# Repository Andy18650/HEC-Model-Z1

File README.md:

# HEC Model Z1
 A Z80 computer with protected mode support
This repository is currently for my own use and for the public to track the progress of the project. 
It is not meant to be used to produce a working computer befor first beta revision is announced.
Any part of this repository may change without notice.

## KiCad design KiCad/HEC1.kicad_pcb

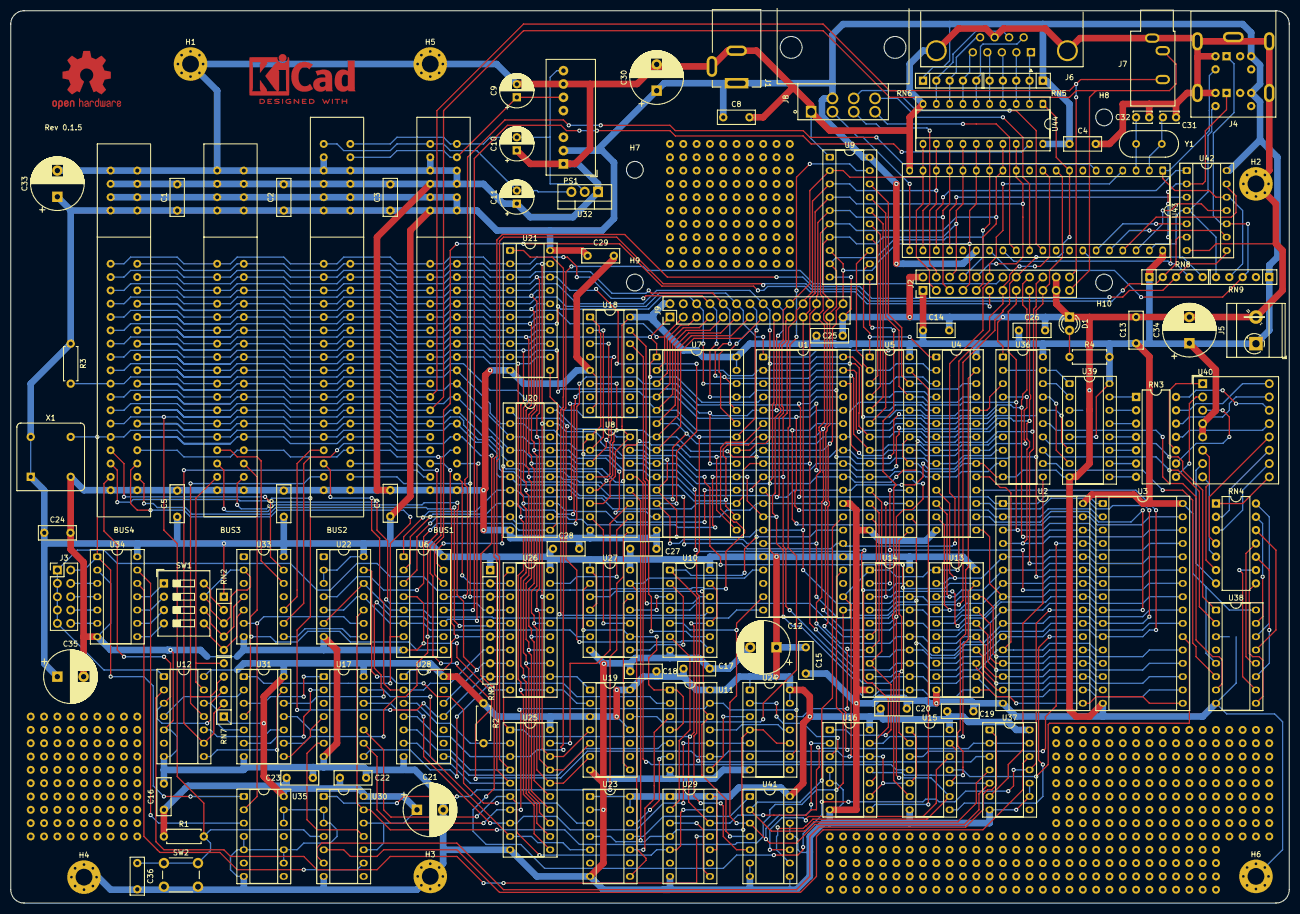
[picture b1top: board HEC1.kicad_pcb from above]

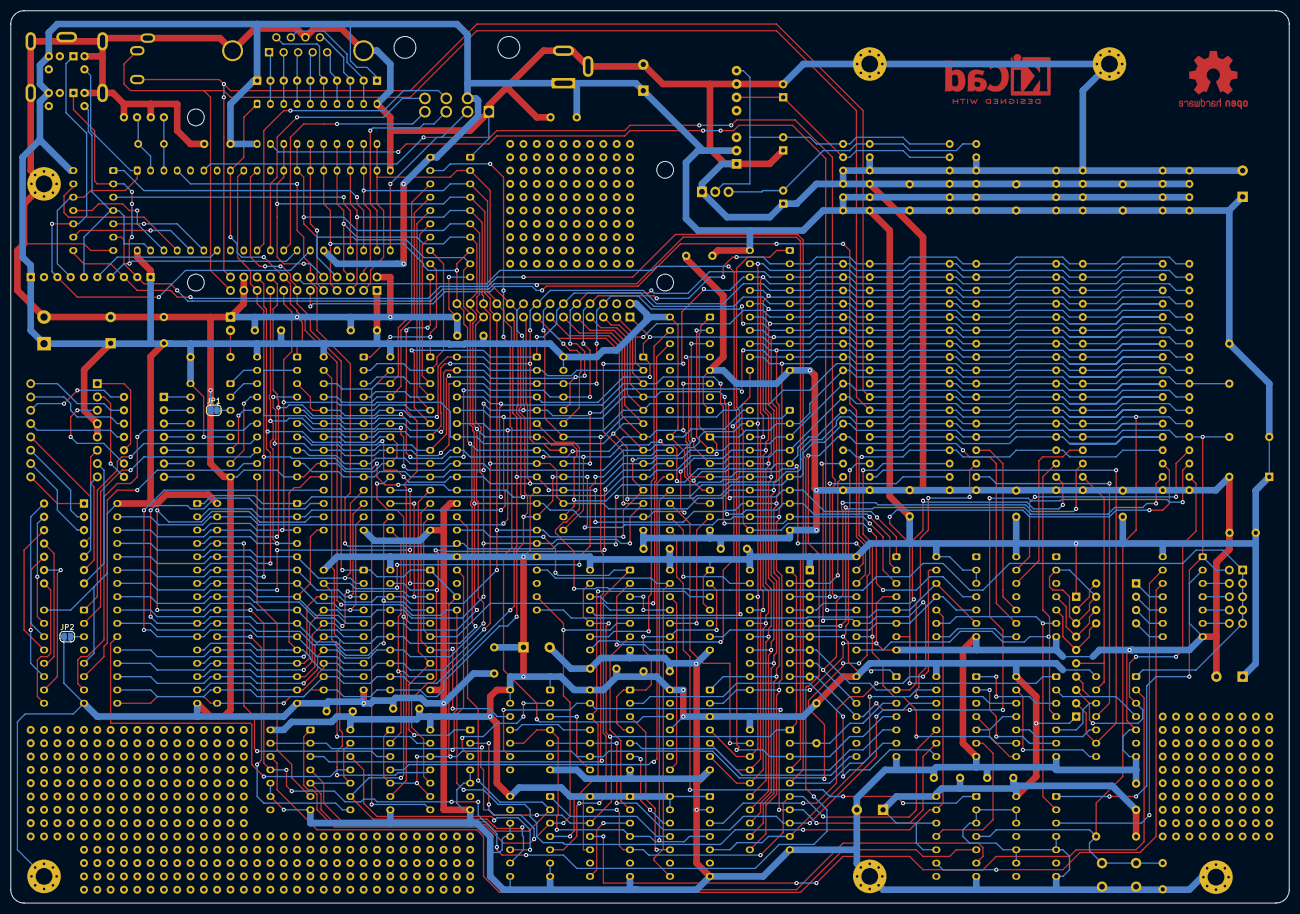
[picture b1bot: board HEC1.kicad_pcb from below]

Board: 2 copper layers, 243.8 x 170.2 mm, 124 parts (2 on the bottom side), 232 nets.

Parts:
BUS1, BUS2: Bus_HEC
BUS3, BUS4: Bus_HEC_5Vonly
C1, C2, C3, C4, C5, C6, C7, C8, C13, C14, C15, C16, C17, C18, C19, C20, C22, C23, C24, C25, C26, C27, C28, C29, C36: C; C_Disc_D7.0mm_W2.5mm_P5.00mm
C9, C10, C11: C_Polarized; CP_Radial_D6.3mm_P2.50mm
C12, C21, C30, C33, C34, C35: C_Polarized; CP_Radial_D10.0mm_P5.00mm
C31, C32: C; C_Disc_D3.4mm_W2.1mm_P2.50mm
D1: LED; LED_D3.0mm
H1, H2, H3, H4, H5, H6: MountingHole_Pad; MountingHole_3.2mm_M3_Pad_Via
H7, H8, H9, H10: MountingHole; MountingHole_3.2mm_M3
J1: Barrel_Jack_Switch; BarrelJack_Kycon_KLDX-0202-xC_Horizontal
J2: Conn_02x12_Odd_Even; PinHeader_2x12_P2.54mm_Vertical
J3: Conn_02x05_Odd_Even; PinHeader_2x05_P2.54mm_Vertical
J4: Connector_double_mini-DIN_6
J5: Screw_Terminal_01x02; TerminalBlock_MetzConnect_Type073_RT02602HBLU_1x02_P5.08mm_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
J6: DE9_Plug_MountingHoles; DSUB-9_Male_Horizontal_P2.77x2.84mm_EdgePinOffset4.94mm_Hou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
J7: AudioJack3; Jack_3.5mm_CUI_SJ1-3533NG_Horizontal
J8: NES_Port_Male; NES_Port_Male_Horizontal
J9: Conn_02x14_Odd_Even; PinHeader_2x14_P2.54mm_Vertical
JP1, JP2: SolderJumper_2_Open; SolderJumper-2_P1.3mm_Open_RoundedPad1.0x1.5mm
PS1: ITX0512S; Converter_DCDC_XP_POWER-ITxxxxxS_THT
R1, R2, R3, R4: R; R_Axial_DIN0207_L6.3mm_D2.5mm_P7.62mm_Horizontal
RN1: R_Network08; R_Array_SIP9
RN2, RN5, RN6, RN7, RN8, RN9: R_Network04; R_Array_SIP5
RN3, RN4: R_Pack07; DIP-14_W7.62mm
SW1: SW_DIP_x04; SW_DIP_SPSTx04_Slide_9.78x12.34mm_W7.62mm_P2.54mm
SW2: SW_Push; SW_PUSH_6mm
U1: Z80CPU; DIP-40_W15.24mm_Socket_ThinPads
U2, U3: AS6C4008-55PCN; DIP-32_W15.24mm_Socket_ThinPads
U4, U5: CY7C199; DIP-28_W7.62mm_Socket_ThinPads
U6, U8, U18: 74LS138; DIP-16_W7.62mm_Socket_ThinPads
U7: 28C256; DIP-28_W15.24mm_Socket_ThinPads
U9, U20, U21, U36: 74LS574; DIP-20_W7.62mm_Socket_ThinPads
U10, U15, U16, U31, U37: 74LS32; DIP-14_W7.62mm_Socket_ThinPads
U11: 74LS00; DIP-14_W7.62mm_Socket_ThinPads
U12: 74LS04; DIP-14_W7.62mm_Socket_ThinPads
U13, U14: 74LS245; DIP-20_W7.62mm_Socket_ThinPads
U17, U33: 74LS20; DIP-14_W7.62mm_Socket_ThinPads
U19, U28: 74LS30; DIP-14_W7.62mm_Socket_ThinPads
U22, U41: 74LS02; DIP-14_W7.62mm_Socket_ThinPads
U23, U24, U27, U29, U30: 74LS74; DIP-14_W7.62mm_Socket_ThinPads
U25, U26, U44: 74LS541; DIP-20_W7.62mm_Socket_ThinPads
U32: LM79M05_TO220; TO-220-3_Vertical
U34: 74LS393; DIP-14_W7.62mm_Socket_ThinPads
U35: 74LS08; DIP-14_W7.62mm_Socket_ThinPads
U38, U39: 74LS47; DIP-16_W7.62mm_Socket_ThinPads
U40: DA04-11EWA; DA04-11SURKWA
U42: 74LS06; DIP-14_W7.62mm_Socket_ThinPads
U43: DIP-40_W15.24mm_Socket_ThinPads
X1: CXO_DIP8; Oscillator_DIP-8
Y1: Crystal; Crystal_HC18-U_Vertical

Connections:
/HEC_CPU/CLK: J3.1, J3.3, J3.5, J3.7, J3.9, U1.6 (~CLK), U12.1
/HEC_CPU/~IOPORT_H: U10.12, U18.14 (O1)
/HEC_CPU/~IOPORT_L: U10.9, U18.15 (O0)
/HEC_CPU/~IORQ: U1.20 (~IORQ), U6.5 (E2), U22.6, U22.12
/HEC_CPU/~MREQ: U1.19 (~MREQ), U10.5, U15.10, U15.13, U16.2, U37.5, U41.3
/HEC_CPU/~NMI: U1.17 (~NMI), U23.8 (~Q), U27.13 (~R)
/HEC_CPU/~RAMEN: U8.9 (O6), U30.1 (~R)
/HEC_CPU/~RD: J2.16, U1.21 (~RD), U10.10, U10.13, U25.1 (G1), U26.1 (G1), U29.12 (D), U37.2, U37.13, U43.8 (~RD), U44.1 (G1)
/HEC_CPU/~RESET: BUS1.25 (~RESET), BUS2.25 (~RESET), BUS3.25 (~RESET), BUS4.25 (~RESET), C36.1, J2.12, R1.2, SW2.1, U1.26 (~RESET), U30.4 (~S), U43.4 (~RESET)
/HEC_CPU/~RFSH: U1.28 (~RFSH), U37.4, U41.2
/HEC_CPU/~WAIT: U1.24 (~WAIT), U22.10, U30.13 (~R)
/HEC_CPU/~WR: BUS1.30 (~IOW), BUS2.30 (~IOW), BUS3.30 (~IOW), BUS4.30 (~IOW), J2.13, U1.22 (~WR), U11.9, U13.1 (A->B), U14.1 (A->B), U15.1, U15.5, U16.9, U16.12, U43.10 (~WR)
/HEC_IO/+12V: BUS1.P4 (+12V), BUS2.P4 (+12V), C9.1, PS1.6 (+Vout)
/HEC_IO/-5V: BUS1.P1 (-5V), BUS2.P1 (-5V), C11.2, U32.3 (VO)
/HEC_IO/-12V: BUS1.P2 (-12V), BUS2.P2 (-12V), C10.2, PS1.8 (-Vout), U32.2 (VI)
/HEC_IO/A0: BUS1.18 (PA0), BUS2.18 (PA0), BUS3.18 (PA0), BUS4.18 (PA0), J2.19, J9.19, U1.30 (A0), U2.27 (A8), U3.27 (A8), U7.10 (A0), U8.1 (A0), U18.1 (A0), U20.2 (D0), U43.9 (A0)
/HEC_IO/A1: BUS1.20 (PA1), BUS2.20 (PA1), BUS3.20 (PA1), BUS4.20 (PA1), J2.20, J9.17, U1.31 (A1), U2.28 (A13), U3.28 (A13), U7.9 (A1), U8.2 (A1), U18.2 (A1), U20.3 (D1)
/HEC_IO/A2: BUS1.22 (PA2), BUS2.22 (PA2), BUS3.22 (PA2), BUS4.22 (PA2), J2.17, J9.15, U1.32 (A2), U2.4 (A12), U3.4 (A12), U7.8 (A2), U8.3 (A2), U18.3 (A2), U20.4 (D2)
/HEC_IO/A3: BUS1.24 (PA3), BUS2.24 (PA3), BUS3.24 (PA3), BUS4.24 (PA3), J2.18, J9.13, U1.33 (A3), U2.30 (A17), U3.30 (A17), U7.7 (A3), U8.5 (E2), U18.6 (E3), U20.5 (D3)
/HEC_IO/A4: BUS1.26 (PA4), BUS2.26 (PA4), BUS3.26 (PA4), BUS4.26 (PA4), J2.15, J9.11, U1.34 (A4), U2.3 (A14), U3.3 (A14), U7.6 (A4), U20.6 (D4)
/HEC_IO/A5: J9.9, U1.35 (A5), U2.31 (A15), U3.31 (A15), U6.1 (A0), U7.5 (A5), U20.7 (D5)
/HEC_IO/A6: J9.7, U1.36 (A6), U2.2 (A16), U3.2 (A16), U6.2 (A1), U7.4 (A6), U20.8 (D6)
/HEC_IO/A7: J9.5, U1.37 (A7), U2.1 (A18), U3.1 (A18), U6.3 (A2), U7.3 (A7), U20.9 (D7)
/HEC_IO/A8: BUS1.1 (A0), BUS2.1 (A0), BUS3.1 (A0), BUS4.1 (A0), J9.8, U1.38 (A8), U4.21 (A0), U5.21 (A0), U7.25 (A8), U21.2 (D0), U36.4 (D2)
/HEC_IO/A9: BUS1.3 (A1), BUS2.3 (A1), BUS3.3 (A1), BUS4.3 (A1), J9.10, U1.39 (A9), U4.23 (A1), U5.23 (A1), U7.24 (A9), U21.3 (D1), U36.2 (D0)
/HEC_IO/A10: BUS1.5 (A2), BUS2.5 (A2), BUS3.5 (A2), BUS4.5 (A2), J9.16, U1.40 (A10), U4.24 (A2), U5.24 (A2), U7.21 (A10), U21.4 (D2), U36.3 (D1)
/HEC_IO/A11: BUS1.7 (A3), BUS2.7 (A3), BUS3.7 (A3), BUS4.7 (A3), J9.12, U1.1 (A11), U4.6 (A10), U5.6 (A10), U7.23 (A11), U21.5 (D3), U36.5 (D3)
/HEC_IO/A12: BUS1.9 (A4), BUS2.9 (A4), BUS3.9 (A4), BUS4.9 (A4), J9.3, U1.2 (A12), U4.7 (A11), U5.7 (A11), U7.2 (A12), U21.6 (D4), U36.6 (D4)
/HEC_IO/A13: BUS1.11 (A5), BUS2.11 (A5), BUS3.11 (A5), BUS4.11 (A5), J9.6, U1.3 (A13), U4.8 (A12), U5.8 (A12), U7.26 (A13), U21.7 (D5), U36.7 (D5)
/HEC_IO/A14: BUS1.13 (A6), BUS2.13 (A6), BUS3.13 (A6), BUS4.13 (A6), J9.1, U1.4 (A14), U4.9 (A13), U5.9 (A13), U7.1 (A14), U21.8 (D6), U36.8 (D6)
/HEC_IO/A15: BUS1.15 (A7), BUS2.15 (A7), BUS3.15 (A7), BUS4.15 (A7), J9.18, U1.5 (A15), U4.10 (A14), U5.10 (A14), U7.20 (~CS), U21.9 (D7), U36.9 (D7)
/HEC_IO/AUDIO_L: BUS1.21 (AUDIO_L), BUS2.21 (AUDIO_L), BUS3.21 (AUDIO_L), BUS4.21 (AUDIO_L), J2.24, J7.R
/HEC_IO/AUDIO_R: BUS1.23 (AUDIO_R), BUS2.23 (AUDIO_R), BUS3.23 (AUDIO_R), BUS4.23 (AUDIO_R), J2.23, J7.T
/HEC_IO/D0: BUS1.2 (D0), BUS2.2 (D0), BUS3.2 (D0), BUS4.2 (D0), J2.10, J9.21, U1.14 (D0), U2.21 (DQ7), U3.21 (DQ7), U7.11 (D0), U9.4 (D2), U13.18 (B0), U14.18 (B0), U19.4, U20.19 (Q0), U21.19 (Q0), U25.18 (Y0), U26.18 (Y0), U43.12 (D0), U44.18 (Y0)
/HEC_IO/D1: BUS1.4 (D1), BUS2.4 (D1), BUS3.4 (D1), BUS4.4 (D1), J2.9, J9.23, U1.15 (D1), U2.13 (DQ0), U3.13 (DQ0), U7.12 (D1), U9.6 (D4), U13.17 (B1), U14.17 (B1), U19.5, U20.18 (Q1), U21.18 (Q1), U25.17 (Y1), U26.17 (Y1), U43.13 (D1), U44.17 (Y1)
/HEC_IO/D2: BUS1.6 (D2), BUS2.6 (D2), BUS3.6 (D2), BUS4.6 (D2), J2.8, J9.25, U1.12 (D2), U2.20 (DQ6), U3.20 (DQ6), U7.13 (D2), U9.9 (D7), U13.16 (B2), U14.16 (B2), U19.6, U20.17 (Q2), U21.17 (Q2), U25.16 (Y2), U26.16 (Y2), U43.14 (D2), U44.16 (Y2)
/HEC_IO/D3: BUS1.8 (D3), BUS2.8 (D3), BUS3.8 (D3), BUS4.8 (D3), J2.7, J9.28, U1.8 (D3), U2.14 (DQ1), U3.14 (DQ1), U7.15 (D3), U9.8 (D6), U13.15 (B3), U14.15 (B3), U20.16 (Q3), U21.16 (Q3), U25.15 (Y3), U26.15 (Y3), U43.15 (D3), U44.15 (Y3)
/HEC_IO/D4: BUS1.10 (D4), BUS2.10 (D4), BUS3.10 (D4), BUS4.10 (D4), J2.6, J9.26, U1.7 (D4), U2.19 (DQ5), U3.19 (DQ5), U7.16 (D4), U9.7 (D5), U13.14 (B4), U14.14 (B4), U20.15 (Q4), U21.15 (Q4), U25.14 (Y4), U26.14 (Y4), U43.16 (D4), U44.14 (Y4)
/HEC_IO/D5: BUS1.12 (D5), BUS2.12 (D5), BUS3.12 (D5), BUS4.12 (D5), J2.5, J9.24, U1.9 (D5), U2.15 (DQ2), U3.15 (DQ2), U7.17 (D5), U9.5 (D3), U13.13 (B5), U14.13 (B5), U20.14 (Q5), U21.14 (Q5), U25.13 (Y5), U26.13 (Y5), U43.17 (D5), U44.13 (Y5)
/HEC_IO/D6: BUS1.14 (D6), BUS2.14 (D6), BUS3.14 (D6), BUS4.14 (D6), J2.4, J9.22, U1.10 (D6), U2.18 (DQ4), U3.18 (DQ4), U7.18 (D6), U9.3 (D1), U13.12 (B6), U14.12 (B6), U19.1, U20.13 (Q6), U21.13 (Q6), U25.12 (Y6), U26.12 (Y6), U43.18 (D6), U44.12 (Y6)
/HEC_IO/D7: BUS1.16 (D7), BUS2.16 (D7), BUS3.16 (D7), BUS4.16 (D7), J2.3, J9.20, U1.13 (D7), U2.17 (DQ3), U3.17 (DQ3), U7.19 (D7), U9.2 (D0), U13.11 (B7), U14.11 (B7), U19.2, U20.12 (Q7), U21.12 (Q7), U25.11 (Y7), U26.11 (Y7), U43.19 (D7), U44.11 (Y7)
/HEC_IO/OSC: BUS1.27 (OSC), BUS2.27 (OSC), BUS3.27 (OSC), BUS4.27 (OSC), J3.2, U34.1 (CP), U35.1, X1.5 (OUT)
/HEC_IO/~IOR: BUS1.28 (~IOR), BUS2.28 (~IOR), BUS3.28 (~IOR), BUS4.28 (~IOR), U2.24 (OE#), U3.24 (OE#), U37.11
/HEC_IO/~IO_CS0: U6.15 (O0), U8.4 (E1), U18.4 (E1)
/HEC_IO/~IO_CS1: J2.11, U6.14 (O1)
/HEC_IO/~IO_CS2: U6.13 (O2), U43.6 (~CS)
/HEC_IO/~IO_CS3: U6.12 (O3), U44.19 (G2)
/HEC_IO/~IO_CS4: BUS1.32 (~IOCS), U6.11 (O4), U31.12
/HEC_IO/~IO_CS5: BUS2.32 (~IOCS), U6.10 (O5), U31.9
/HEC_IO/~IO_CS6: BUS3.32 (~IOCS), U6.9 (O6), U31.4
/HEC_IO/~IO_CS7: BUS4.32 (~IOCS), U6.7 (O7), U31.1
/HEC_IO/~IRQ1: BUS1.31 (~IRQ), RN1.6 (R5), U26.6 (A4), U28.1
/HEC_IO/~IRQ2: BUS2.31 (~IRQ), RN1.7 (R6), U26.7 (A5), U28.2
/HEC_IO/~IRQ3: BUS3.31 (~IRQ), RN1.8 (R7), U26.8 (A6), U28.12
/HEC_IO/~IRQ4: BUS4.31 (~IRQ), RN1.9 (R8), U26.9 (A7), U28.11
/HEC_IO/~NOWS1: BUS1.33 (~NOWS), RN7.2 (R1), U12.9
/HEC_IO/~NOWS2: BUS2.33 (~NOWS), RN7.4 (R3), U12.11
/HEC_IO/~NOWS3: BUS3.33 (~NOWS), RN7.5 (R4), U12.13
/HEC_IO/~NOWS4: BUS4.33 (~NOWS), RN7.3 (R2), U12.3
/HEC_IO/~ROM_OE: BUS1.17 (~ROMR), BUS2.17 (~ROMR), BUS3.17 (~ROMR), BUS4.17 (~ROMR), J9.14, U7.22 (~OE), U37.3
/HEC_IO/~ROM_WE: BUS1.19 (~ROMW), BUS2.19 (~ROMW), BUS3.19 (~ROMW), BUS4.19 (~ROMW), R3.2
/HEC_IO/~SENSE1: BUS1.34 (~SENSE), RN1.2 (R1), U26.2 (A0)
/HEC_IO/~SENSE2: BUS2.34 (~SENSE), RN1.3 (R2), U26.3 (A1)
/HEC_IO/~SENSE3: BUS3.34 (~SENSE), RN1.4 (R3), U26.4 (A2)
/HEC_IO/~SENSE4: BUS4.34 (~SENSE), RN1.5 (R4), U26.5 (A3)
/HEC_IO/~WAIT1: BUS1.29 (~WAIT), U33.9
/HEC_IO/~WAIT2: BUS2.29 (~WAIT), U33.10
/HEC_IO/~WAIT3: BUS3.29 (~WAIT), U33.12
/HEC_IO/~WAIT4: BUS4.29 (~WAIT), U33.13
/HEC_Memory/ATTR_NX: U5.12 (D1), U14.7 (A5), U24.12 (D)
/HEC_Memory/ATTR_RI: U5.13 (D2), U10.4, U14.6 (A4)
/HEC_Memory/ATTR_WI: U5.11 (D0), U14.8 (A6), U16.1
/HEC_Memory/ATTR_WP: U5.15 (D3), U14.9 (A7), U15.2
/HEC_Memory/PROC_ID0: U4.25 (A3), U5.25 (A3), U9.17 (Q2)
/HEC_Memory/PROC_ID1: U4.4 (A8), U5.4 (A8), U9.15 (Q4)
/HEC_Memory/PROC_ID2: U4.1 (A5), U5.1 (A5), U9.12 (Q7)
/HEC_Memory/PROC_ID3: U4.2 (A6), U5.2 (A6), U9.13 (Q6)
/HEC_Memory/PROC_ID4: U4.3 (A7), U5.3 (A7), U9.14 (Q5)
/HEC_Memory/PROC_ID5: U4.5 (A9), U5.5 (A9), U9.16 (Q3)
/HEC_Memory/PROC_ID6: U4.26 (A4), U5.26 (A4), U9.18 (Q1)
/HEC_Memory/RAM_A8: U2.5 (A7), U3.5 (A7), U4.11 (D0), U13.2 (A0)
/HEC_Memory/RAM_A9: U2.6 (A6), U3.6 (A6), U4.12 (D1), U13.3 (A1)
/HEC_Memory/RAM_A10: U2.7 (A5), U3.7 (A5), U4.13 (D2), U13.4 (A2)
/HEC_Memory/RAM_A11: U2.8 (A4), U3.8 (A4), U4.15 (D3), U13.5 (A3)
/HEC_Memory/RAM_A12: U2.9 (A3), U3.9 (A3), U4.16 (D4), U13.6 (A4)
/HEC_Memory/RAM_A13: U2.10 (A2), U3.10 (A2), U4.17 (D5), U13.7 (A5)
/HEC_Memory/RAM_A14: U2.11 (A1), U3.11 (A1), U4.18 (D6), U13.8 (A6)
/HEC_Memory/RAM_A15: U2.12 (A0), U3.12 (A0), U4.19 (D7), U13.9 (A7)
/HEC_Memory/RAM_A16: U2.26 (A9), U3.26 (A9), U5.18 (D6), U14.2 (A0)
/HEC_Memory/RAM_A17: U2.25 (A11), U3.25 (A11), U5.17 (D5), U14.3 (A1)
/HEC_Memory/RAM_A18: U2.23 (A10), U3.23 (A10), U5.16 (D4), U14.4 (A2)
/HEC_Memory/RAM_A19: U5.19 (D7), U14.5 (A3), U15.9, U41.9
/HEC_Memory/SYSGATE: U9.19 (Q0), U19.12
/HEC_Memory/~PAGE_H_WE: U5.27 (~WE), U16.8
/HEC_Memory/~PAGE_H: U8.14 (O1), U14.19 (CE), U16.10
/HEC_Memory/~PAGE_L_WE: U4.27 (~WE), U16.11
/HEC_Memory/~PAGE_L: U8.15 (O0), U13.19 (CE), U16.13
/HEC_Memory/~PID: U8.13 (O2), U15.4
/HEC_Memory/~RAM0CS: U2.22 (CE#), U15.8
/HEC_Memory/~RAM1CS: U3.22 (CE#), U15.11
/HEC_Memory/~RAM_A19: U15.12, U41.10
/HEC_Memory/~RAM_WR: U2.29 (WE#), U3.29 (WE#), U15.3
/HEC_Peripherals/~KB_IRQ: RN8.2 (R1), U25.4 (A2), U28.5, U42.6
/HEC_Peripherals/~MS_IRQ: RN8.3 (R2), U25.5 (A3), U28.6, U42.8
/HEC_Protection/M1: U11.12, U27.3 (C), U41.4
/HEC_Protection/SYS: U6.6 (E3), U22.5, U22.11, U27.6 (~Q)
/HEC_Protection/~AUX_IRQ: R2.2, U25.2 (A0), U28.3
/HEC_Protection/~CLRINT: U8.12 (O3), U23.4 (~S), U24.4 (~S), U24.10 (~S), U29.4 (~S)
/HEC_Protection/~GOUSR: U8.7 (O7), U27.10 (~S)
/HEC_Protection/~INT_SOURCE_1: U8.11 (O4), U25.19 (G2)
/HEC_Protection/~INT_SOURCE_2: U8.10 (O5), U26.19 (G2)
/HEC_Protection/~IO_PROT: U17.13, U23.5 (Q), U25.9 (A7)
/HEC_Protection/~M1: U1.27 (~M1), U10.1, U41.5
/HEC_Protection/~RFAULT: U17.10, U25.6 (A4), U29.5 (Q), U29.13 (~R)
/HEC_Protection/~VDP_IRQ: J2.14, U25.3 (A1), U28.4
/HEC_Protection/~WFAULT: U11.10, U17.12, U24.5 (Q), U25.8 (A6)
/HEC_Protection/~XFAULT: U11.13, U17.9, U24.9 (Q), U25.7 (A5)
H: BUS1.P9 (+5V), BUS1.P10 (+5V), BUS1.P11 (+5V), BUS1.P12 (+5V), BUS2.P9 (+5V), BUS2.P10 (+5V), BUS2.P11 (+5V), BUS2.P12 (+5V), BUS3.P9 (+5V), BUS3.P10 (+5V), BUS3.P11 (+5V), BUS3.P12 (+5V), BUS4.P9 (+5V), BUS4.P10 (+5V), BUS4.P11 (+5V), BUS4.P12 (+5V), C1.1, C2.1, C3.1, C4.1, C5.1, C6.1, C7.1, C8.1, C12.1, C13.1, C14.1, C15.1, C16.1, C17.1, C18.1, C19.1, C20.1, C21.1, C22.1, C23.1, C24.1, C25.1, C26.1, C27.1, C28.1, C29.1, C30.1, C33.1, C34.1, C35.1, J1.1, J2.1, J4.A4, J4.B4, J5.1, J8.7 (VDD), J9.2, PS1.2 (+Vin), R1.1, R2.1, R3.1, R4.2, RN1.1 (common), RN2.1 (common), RN5.1 (common), RN6.1 (common), RN7.1 (common), RN8.1 (common), RN9.1 (common), U1.11 (VCC), U1.16 (~INT), U1.25 (~BUSRQ), U2.32 (VCC), U3.32 (VCC), U4.28 (VCC), U5.28 (VCC), U6.16 (VCC), U7.27 (~WE), U7.28 (VCC), U8.6 (E3), U8.16 (VCC), U9.20 (VCC), U10.14 (VCC), U11.14 (VCC), U12.14 (VCC), U13.20 (VCC), U14.20 (VCC), U15.14 (VCC), U16.14 (VCC), U17.14 (VCC), U18.16 (VCC), U19.3, U19.11, U19.14 (VCC), U20.20 (VCC), U21.20 (VCC), U22.2, U22.3, U22.14 (VCC), U23.1 (~R), U23.13 (~R), U23.14 (VCC), U24.1 (~R), U24.13 (~R), U24.14 (VCC), U25.20 (VCC), U26.20 (VCC), U27.1 (~R), U27.4 (~S), U27.14 (VCC), U28.14 (VCC), U29.1 (~R), U29.10 (~S), U29.14 (VCC), U30.10 (~S), U30.12 (D), U30.14 (VCC), U31.14 (VCC), U33.14 (VCC), U34.14 (VCC), U35.14 (VCC), U36.20 (VCC), U37.14 (VCC), U38.5 (RBI), U38.16 (VCC), U39.5 (RBI), U39.16 (VCC), U40.4 (DIG1_CA), U40.5 (DIG2_CA), U41.14 (VCC), U42.14 (VCC), U43.26 (TEST), U43.40 (VCC), U44.20 (VCC), X1.1 (EN), X1.8 (Vcc)
L: BUS1.35 (GND), BUS1.36 (GND), BUS1.P3 (GND), BUS1.P5 (GND), BUS1.P6 (GND), BUS1.P7 (GND), BUS1.P8 (GND), BUS2.35 (GND), BUS2.36 (GND), BUS2.P3 (GND), BUS2.P5 (GND), BUS2.P6 (GND), BUS2.P7 (GND), BUS2.P8 (GND), BUS3.35 (GND), BUS3.36 (GND), BUS3.P5 (GND), BUS3.P6 (GND), BUS3.P7 (GND), BUS3.P8 (GND), BUS4.35 (GND), BUS4.36 (GND), BUS4.P5 (GND), BUS4.P6 (GND), BUS4.P7 (GND), BUS4.P8 (GND), C1.2, C2.2, C3.2, C4.2, C5.2, C6.2, C7.2, C8.2, C9.2, C10.1, C11.1, C12.2, C13.2, C14.2, C15.2, C16.2, C17.2, C18.2, C19.2, C20.2, C21.2, C22.2, C23.2, C24.2, C25.2, C26.2, C27.2, C28.2, C29.2, C30.2, C31.1, C32.1, C33.2, C34.2, C35.2, C36.2, D1.1 (K), H1.1, H2.1, H3.1, H4.1, H5.1, H6.1, J1.2, J1.3, J2.2, J2.21, J2.22, J4.A3, J4.B3, J4.SH, J5.2, J6.0 (PAD), J6.8, J7.S, J8.1 (GND), J9.27, JP1.1 (A), JP2.1 (A), PS1.1 (-Vin), PS1.7 (Common), SW2.2, U1.29 (GND), U2.16 (VSS), U3.16 (VSS), U4.14 (GND), U4.20 (~CE), U4.22 (~OE), U5.14 (GND), U5.20 (~CE), U5.22 (~OE), U6.4 (E1), U6.8 (GND), U7.14 (GND), U8.8 (GND), U9.1 (OE), U9.10 (GND), U10.7 (GND), U11.7 (GND), U12.5, U12.7 (GND), U13.10 (GND), U14.10 (GND), U15.7 (GND), U16.4, U16.5, U16.7 (GND), U17.7 (GND), U18.5 (E2), U18.8 (GND), U19.7 (GND), U20.10 (GND), U21.10 (GND), U22.7 (GND), U23.2 (D), U23.7 (GND), U24.7 (GND), U25.10 (GND), U26.10 (GND), U27.7 (GND), U28.7 (GND), U29.7 (GND), U30.2 (D), U30.3 (C), U30.7 (GND), U31.7 (GND), U32.1 (GND), U33.7 (GND), U34.2 (MR), U34.7 (GND), U35.4, U35.5, U35.7 (GND), U35.9, U35.10, U35.12, U35.13, U36.1 (OE), U36.10 (GND), U37.7 (GND), U37.9, U37.10, U38.8 (GND), U39.8 (GND), U41.6, U41.7 (GND), U41.8, U41.11, U41.12, U42.7 (GND), U43.20 (GND), U44.10 (GND), X1.4 (GND)
unnamed: D1.2 (A), R4.1
unnamed: J3.4, U34.3 (Q0)
unnamed: J3.6, U34.4 (Q1)
unnamed: J3.8, U34.5 (Q2)
unnamed: J3.10, U34.6 (Q3)
unnamed: J8.2 (CLK), U43.21 (RC)
unnamed: J8.6 (D3), U43.31 (P14)
unnamed: J8.5 (D4), U43.30 (P13)
unnamed: J8.4 (DATA), U43.29 (P12)
unnamed: J8.3 (LATCH), U43.22 (A20)
unnamed: JP1.2 (B), U39.3 (LT)
unnamed: JP2.2 (B), U38.3 (LT)
unnamed: RN2.2 (R1), SW1.8, U33.1
unnamed: RN2.3 (R2), SW1.7, U33.2
unnamed: RN2.4 (R3), SW1.6, U33.4
unnamed: RN2.5 (R4), SW1.5, U33.5
unnamed: RN3.1 (R1.1), U39.15 (f)
unnamed: RN3.14 (R1.2), U40.14 (DIG1_F)
unnamed: RN3.2 (R2.1), U39.14 (g)
unnamed: RN3.13 (R2.2), U40.16 (DIG1_G)
unnamed: RN3.3 (R3.1), U39.13 (a)
unnamed: RN3.12 (R3.2), U40.15 (DIG1_A)
unnamed: RN3.4 (R4.1), U39.12 (b)
unnamed: RN3.11 (R4.2), U40.13 (DIG1_B)
unnamed: RN3.5 (R5.1), U39.11 (c)
unnamed: RN3.10 (R5.2), U40.1 (DIG1_C)
unnamed: RN3.6 (R6.1), U39.10 (d)
unnamed: RN3.9 (R6.2), U40.3 (DIG1_D)
unnamed: RN3.7 (R7.1), U39.9 (e)
unnamed: RN3.8 (R7.2), U40.2 (DIG1_E)
unnamed: RN4.1 (R1.1), U40.9 (DIG2_G)
unnamed: RN4.14 (R1.2), U38.14 (g)
unnamed: RN4.2 (R2.1), U40.11 (DIG2_F)
unnamed: RN4.13 (R2.2), U38.15 (f)
unnamed: RN4.3 (R3.1), U40.10 (DIG2_A)
unnamed: RN4.12 (R3.2), U38.13 (a)
unnamed: RN4.4 (R4.1), U40.12 (DIG2_B)
unnamed: RN4.11 (R4.2), U38.12 (b)
unnamed: RN4.5 (R5.1), U40.8 (DIG2_C)
unnamed: RN4.10 (R5.2), U38.11 (c)
unnamed: RN4.6 (R6.1), U40.6 (DIG2_D)
unnamed: RN4.9 (R6.2), U38.10 (d)
unnamed: RN4.7 (R7.1), U40.7 (DIG2_E)
unnamed: RN4.8 (R7.2), U38.9 (e)
unnamed: J6.1, RN5.2 (R1), U44.2 (A0)
unnamed: J6.2, RN5.3 (R2), U44.3 (A1)
unnamed: J6.3, RN5.4 (R3), U44.4 (A2)
unnamed: J6.4, RN5.5 (R4), U44.5 (A3)
unnamed: J6.7, RN6.2 (R1), U44.9 (A7)
unnamed: J6.9, RN6.3 (R2), U44.8 (A6)
unnamed: J6.5, RN6.4 (R3), U44.7 (A5)
unnamed: J6.6, RN6.5 (R4), U44.6 (A4)
unnamed: J4.B1, RN8.4 (R3), U42.2, U43.28 (P11/MSDI)
unnamed: RN8.5 (R4), U43.34 (~KBD_INH)
unnamed: J4.A1, RN9.3 (R2), U42.10, U43.27 (P10/KBDI)
unnamed: J4.A5, RN9.4 (R3), U42.12, U43.1 (KBCI)
unnamed: J4.B5, RN9.5 (R4), U42.4, U43.39 (KBDI/MSCI)
unnamed: U9.11 (Cp), U15.6
unnamed: U11.2, U17.8
unnamed: U11.5, U28.8
unnamed: U12.4, U31.2
unnamed: U12.8, U31.13
unnamed: U12.10, U31.10
unnamed: U12.12, U31.5
unnamed: U17.1, U31.3
unnamed: U17.2, U31.6
unnamed: U17.4, U31.8
unnamed: U17.5, U31.11
unnamed: U20.11 (Cp), U21.11 (Cp), U22.4
unnamed: U10.8, U20.1 (OE)
unnamed: U10.11, U21.1 (OE)
unnamed: U22.8, U33.8
unnamed: U22.9, U33.6, U35.2
unnamed: U22.13, U23.3 (C)
unnamed: U23.11 (C), U41.1
unnamed: U11.6, U23.12 (D)
unnamed: U11.3, U23.10 (~S)
unnamed: U11.8, U24.3 (C)
unnamed: U16.3, U24.2 (D)
unnamed: U11.11, U24.11 (C)
unnamed: U11.1, U11.4, U27.2 (D), U27.9 (Q)
unnamed: U10.3, U27.11 (C)
unnamed: U19.8, U27.12 (D)
unnamed: U10.2, U27.8 (~Q)
unnamed: U29.3 (C), U29.8 (~Q)
unnamed: U10.6, U29.2 (D)
unnamed: U12.2, U29.11 (C)
unnamed: U30.5 (Q), U37.12
unnamed: U30.6 (~Q), U37.1
unnamed: U17.6, U30.11 (C)
unnamed: U30.9 (Q), U34.12 (MR)
unnamed: U34.13 (CP), U35.3
unnamed: SW1.1, U34.11 (Q0)
unnamed: SW1.2, U34.10 (Q1)
unnamed: SW1.3, U34.9 (Q2)
unnamed: SW1.4, U34.8 (Q3)
unnamed: U36.11 (Cp), U37.6
unnamed: U36.19 (Q0), U39.1 (B)
unnamed: U36.18 (Q1), U39.2 (C)
unnamed: U36.17 (Q2), U39.7 (A)
unnamed: U36.16 (Q3), U39.6 (D)
unnamed: U36.15 (Q4), U38.7 (A)
unnamed: U36.14 (Q5), U38.1 (B)
unnamed: U36.13 (Q6), U38.2 (C)
unnamed: U36.12 (Q7), U38.6 (D)
unnamed: U42.13, U43.37 (KBCO)
unnamed: U42.11, U43.38 (KBDO)
unnamed: U42.5, U43.35 (KB_OBFO)
unnamed: U42.9, U43.36 (MS_OBFO)
unnamed: C31.2, U43.2 (OSCI), Y1.1
unnamed: C32.2, U43.3 (OSCO), Y1.2
unnamed: U42.1, U43.23 (P22/MSDO)
unnamed: U42.3, U43.24 (P23/MSCO)

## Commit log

2024-03-06 Initial Commit
    Add existing files to the repo to manage with Git
2024-03-06 Added a simple README file
2024-03-07 Update NMI timing circuit
    Updated the NMI generation circuit to prevent a bug occurring when NMI is generated between the rising edge of the last T cycle of an instruction and the falling edge of M1 of the next. Due to delay 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
2024-03-07 Create .gitignore file
    Created a .gitegnore file to ignore all automatic backups created by KiCad.
2024-03-07 Add NMI reset circuit
    Added a circuit that will reset /NMI state for the HEC and allow further NMI when /INTEN or /GOUSR port is accessed.
2024-03-14 Update to protection circuit
    Update the protection circuit to prevent all interrupts when HEC is in SYS mode
2024-03-15 Add fault generation circuit
    Add circuit to generate fault on illegal read, write and M1 cycle
2024-03-15 Complete fault generation circuit
    Add circuit to generate fault on illegal IO access. The protection circuit design is not considered complete.
2024-03-19 Add HEC Bus
    The HEC bus packs a lot of information into a small amount of pins. It is suitable for cards with various complexity.
2024-03-19 Created footprint for HEC bus
    Created footprints for HEC bus and some other updates.
2024-03-19 IO implementation
    Implemented most of IO functions, add connections between the schematics.
2024-03-19 Add wait state generator
    Add circuit to generate 0 to 15 wait states or use external wait input.
2024-03-19 Saved changes for added save state generator
    Some changes for the wait state generator was not saved in the last commit
2024-03-20 MATX-compliant motherboard
    Made the motherboard mounting holes and card positions MATX compliant. The MATX motherboard edge is shifted 0.5 inches to the left, which is annoying. Also, cards have component on the opposite side 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
2024-03-20 PCB Update
    Some part placement, some routing, some change in schematic for easier PCB routing.
2024-03-20 Add POST code circuit
    Add circuit to show POST code using I register on Z80 to assist debugging.
2024-03-21 Cleanup schematic
    Cleanup the schematic for easier reading, reduce ERC errors.
2024-03-21 Add keyboard circuit
    Added symbol for HT6542B keyboard controller. Added keyboard and mouse support to IO circuit. Reduced ERC error to 0.
2024-03-24 Split peripherals into separate schematic
    Split graphics/sound/storage (VERA) board connector and keyboard/mouse controller into a separate schematic file. Add joystick/controller port. This commit is seriously delayed by the controller port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
2024-04-02 Remove dependencies for Omega Library
    Components from the Omega project did not end up getting used, therefore, they are removed.
2024-04-02 Add NES port
    Added NES port from NES port breadboard project
2024-04-02 Removed DMA from bus
    Bus-mastering DMA has been removed from the expansion bus design due to complexity and bandwidth issue with external bus expansion circuit. The pins are replaced with audio output from on-bard sound 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
2024-04-02 Add Mini-DIN-6 footprint
    It turns out that KiCad had only symbol but not footprint for Mini-DIN-6. Therefore I used a custom one made by 4x1md
2024-04-05 PCB Layout attempt
    Played with PCB layout a bit to get an idea of how the layout of HEC would look like. Minor updates to schematic to simplify PCB layout.
2024-04-08 double Mini DIN 6 port
    Added double Mini DIN 6 port to replace two Mini DIN 6 port to save cost and simplify building process. The footprint is derived from the existing single mini DIN 6 port. With changes according to th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
2024-04-08 Preliminary layout
    Very early stage layout prototype, very subject to change.
2024-04-08 Updated layout
    Updated the layout of PCB. Chips on the board in this version might be in their final position.
2024-04-08 New bus symbol
    Updated bus symbol and footprint to simplify PCB layout.
2024-04-09 Exchange RI and NX pins on bus driver
    A mistake is found in the schematic: the RI and NX bits are exchanged on the 74245 bus driver chip. The mistake has been corrected. This change is significant since it changes the (non-existent) soft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
2024-04-09 Add prototyping region
    Add some prototyping regions to the board, since there WILL be bugs!
2024-04-11 Some routing attempt
    Attempted to route some traces. 2-layer PCB seems to be achievable. It might just be a fool's arrogance.
2024-04-13 More routing
    Swapped U15 and U16, minor adjustments to schematic. routing of power lines.
2024-04-13 Update to bus pinout
    Move /RD and /WR signal closer to /CS to simplify add-on card design for common chips. From a simple search of pinouts of common chips this may reduce the amount of vias needed on the card.
2024-04-14 More routing
    Finished routing the IO part of the board. Currently it doesn't seem like a 4-layer board is needed.
2024-04-14 Livestream routing
    First routing livestream! Routed a data bus and some traces protection and memory region.
2024-04-14 Bug fixes
    fixed some bugs introduced to the schematic. More routing.
2024-04-14 More routing, a power LED
    Did some easier routing. The current concern is that the already done easy routing would take up space for harder to route traces, making them even harder. However, one have to start somewhere... The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
2024-04-15 More routing
    Even more routing... Maybe 50% finished? The remaining 50% is probably harder though.
2024-04-15 Livestream commit
    Committing live! Just to make sure that I don't lose 1 day of work.
2024-04-15 End of livestream
    State of the project at the end of the livestream, still not finished.
2024-04-15 Bottom left routing complete
    Finished routing the bottom left side of the PCB (wait generation and part of protection). Minor changes to schematic to ease routing.
2024-04-15 More routing
    Routing starts to become harder since most of the board is occupied. I should REALLY use a set of constraints that allow me to route two traces between adjacent pads...
2024-04-16 Finish routing data bus
    finished routing arguably the hardest part of the board: the data bus. The routing is mostly complete. However, the rest of traces are very hard to route. One more day of work is expected.
2024-04-16 Preliminary routing
    Changed footprint pad size to allow 2 traces to be routed between adjacent pads. Finished routing all ICs. Bypass caps not added. Some traces may need to be optimized.
2024-04-16 fix DRC errors, generate gerbers
    Fixed all DRC errors (except a few silkscreen clipped warnings). Generated gerber files for first version of the board.
2024-04-25 Correct gerber files
2024-04-26 Created test ROM code
    The test code uses the I register to flash an LED. It just works!
2024-04-26 Fixes to 2 issues found in the first prototype
    Added jumper pads to allow user to switch between 74LS47 and DM9368 7-segment decoder chips, add reset timing capacitor.
2024-04-30 RAM test code
    Test code to load bootloader into RAM and jump (actually, more like fall through) to it. The code runs on current prototype.
2024-05-02 Controller port and wait state test
    Code to test the ATARI controller port and wait state generator. Both worked without issue.
2024-05-02 Create documentation
    Wrote some documentation for the prototype board so people can write software for it.
2024-05-02 Change resistor network, add revision number
    Changed most of the resistor network footprints so that they would accept both 9 pin and 5 pin resistor networks (since I bought 50 of those 5 pin ones!). Power routing optimizations. Added a revisio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
2024-05-09 More testing
2024-05-09 More testing
    Successfully replaced EEPROM with EPROM Emulator NG, much faster testing cycle.
2024-05-13 Change LED display type
    Changed LED display to include two decimal points to indicate usr/sys mode. This type of LED display is easier to source.
2024-06-09 change NX bit to XE bit
    change No eXecute to eXecute Enable (inverting the polarity of the signal) in order to fix a bug that causes the HEC to not recognize a NX when the instruction fetched is a RST.
2024-06-13 Fixed reversed POST code display
    Wrote a program to test the POST code LED display, found out it's backwards, and fixed it in schematic
2024-06-19 VERA bringup
    Brought up VERA, streamlines firmware build process.
2024-06-19 Custom load routine
    Customized EPROM emulator NG load routine to output less lines so that I can see the assembler output.
2024-06-19 Font loading
    successfully loaded font to VERA.
2024-06-19 Proper RAM init
    Initialize RAM properly. Subroutines are working
2024-06-19 Protection Overhaul
    Major change to the protection system. This change WILL break system software compatibility. Previously: bit 15: WP, 1=disable writing; bit 14: WI, 0=generate interrupt on write; bit 13: NX/XE 1/0=ge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
2024-06-19 Finish protection overhaul
    Disable ram chip select when page is marked as not present, change write protect to 1 as write enabled, 0 as disabled. Change XE interrupt timings.
2024-06-21 Library cleanup
    Disabled unused libraries and move used ones to local library.
2024-06-21 Add I2C bus
    Change audio pins on the bus to carry I2C signal. This can be used for configuring onboard devices such as RGB to HDMI converters, sound mixers, GPIOs, etc.
2024-06-21 Fancy power circuit
    Added a circuit to switch power, short press to power on, long press to power off.
2024-07-04 Added 3.3V bus symbols
    Due to demand for bus with 3.3V power supply and signaling, 2 symbols are added. One for a 5V bus with 3.3V supply and one for 3.3V only. The biggest difference other than connector size is that the 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
2024-07-04 Spamming Net-ties
    Spam Net-ties everywhere, replacing old H and L symbols in preparation for a 4-layber board design.
2024-07-05 Remove external ROM emulator connector
    Removed the connector for connecting to ROM emulator. The connector was not a particular success as a 34-pin ribbon cable instead of 28 pin is required. The absence of a reset pin was also a mistake.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
2024-07-05 Add flash circuit
    Changed EEPROM to NOR flash to increase speed. Added circuit to update firmware without requiring a programmer.
2024-07-06 Test code
    Code to test paging, VERA, interrupts KMI and NES controller port.
2024-07-08 Livestream update
    Updates made during last livestream.
2024-07-09 System call test
    Tested several types of system call handlers. The self-modifying code version is chosen for its speed and compactness.
2024-07-19 Start building firmware
    Created firmware folder to develop a firmware for the HEC.
2024-07-30 Add gadgets
    Added 'gadgets' to read/write the page table or memory of another process.
2024-08-01 Add two more gadgets
    Added gadgets for far calling and task switching.
2024-08-06 Updates to circuit
    Updates to the second gen circuit
2024-08-06 SD Card tests
    Testing CMD0 on SD Card, not working so far.
2024-09-02 Updates to schematic
    Unfinished design of V2 schematic
2024-10-13 Update to KiCad 8.0, clean up schematic
    Cleaned up the IO schematic using experience from model 9 schematic. Changed the controller pinout to be compatible with the Kempston standard.
2024-10-13 Completed i2c subsystem
    Updates to schematic, the i2c driver is circuit now complete.
